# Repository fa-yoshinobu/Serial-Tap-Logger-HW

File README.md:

# Serial Tap Logger | RS-232C Rev.1

RS-232C機器2台の間にDE-9オス・メスで挿入し、送受信データと制御線の計8本をmicroSDに記録するロガー。各線を200 kΩ以上の抵抗で分岐し、DE-9の全9ピンを同じ番号で中継します。

## 現在の状況

Rev.1の基板と製造用データを作成済みです。ERC・DRC・未配線・回路図との不一致は各0件。裏面のBOMと実装座標は104点で照合済みです。記録ファームウェアは開発中で、記録性能とケースの嵌合は試作機で確認します。[作業状況と検証結果](docs/Work_Status.md)

## 接続例

[RS-232Cの接続例](docs/Wiring-RS232C.md)に、DE-9オス・メスの挿入位置、送受信を観測する配線、本体電源のつなぎ方を示します。

## 設計・製造資料

| 目的 | 資料 |
| --- | --- |
| 手はんだ部品を用意する | [手はんだ部品表](pcb/manufacturing/Hand_Assembly_BOM.csv) |
| JLCPCBに実装を依頼する | [JLCPCB実装部品表](pcb/manufacturing/PCBA_BOM.csv) |
| 回路を確認する | [回路図PDF](docs/Serial_Tap_Logger_RS232C_Rev1.pdf)・[KiCadデータ](pcb/) |
| 設計と寸法を確認する | [設計資料](docs/Design_Notes.md)・[ピン照合表](docs/Pin_Mapping.csv)・[基板STEP](enclosure/3d-models/Serial_Tap_Logger_RS232C_Rev1_PCBA.step)・[ケース組立](enclosure/drawings/Case_Print_Rev1.md) |
| 基板を製造・実装する | [入稿ファイルと発注条件](docs/Manufacturing.md)・[手はんだ実装図](enclosure/drawings/Hand-Solder-Assembly-Rev1.pdf) |
| 検証結果を確認する | [作業状況と残件](docs/Work_Status.md)・[検証レポート一覧](docs/verification/) |

## 基板の外観

| 表面（操作側）の実装3D図 | 裏面（工場実装側）の実装3D図 |
| --- | --- |
|  |  |

| 表面の配線（F.Cu） | 裏面の配線（B.Cu） |
| --- | --- |
|  |  |

## 主な仕様

| 項目 | 内容 |
| --- | --- |
| 対象 | RS-232C（±3〜±25 V）、115,200 bpsまでが設計目標 |
| 観測 | TXD・RXD・RTS・CTS・DTR・DSR・DCD・RIを正・負・開放（0 V付近）の3状態で判別。RIを除く7本の線路電圧も推定 |
| 記録と操作 | microSD（SDHC）、2.4インチ液晶、ロータリーエンコーダー |
| 基板 | 100 × 100 mm、2層。裏面を工場実装し、コネクタとモジュールを表面に手はんだ |
| 拡張端子 | Grove 2口（J7 I²C、J8 GP22／GP24、各3.3 V） |
| ケース | 3Dプリント用。幅121.1 × 奥行114.05 × 高さ32.8 mm（樹脂ケース単体） |

**測定中はUSBでPCに接続しない。** 電源はDC出力が接地されていない安定化12 V・1 AのACアダプター（外径5.5 mm、内径2.1 mm、センタープラス）を使用します。ログは測定後にmicroSDを取り出して読み込みます。[対応アダプターの例](https://akizukidenshi.com/catalog/g/g117429/)

## 主な部品と選定理由

- **WeAct RP2350B**。PIOで8本の状態を同時に取り込み、ADCで7本の線路電圧を推定するために使います。
- **窓型比較器**。各線の正・負・開放（0 V付近）を判別します。公称の判定点は線路換算で＋2.42 Vと−2.17 Vです。
- **PCF8563と電気二重層コンデンサー**。ログに日時を付け、電源を切っている間も時計を保持します。

## 3Dプリント用ケース

ふたはM3の熱圧入インサートとM3×6 mmねじ各4個で固定します。組立手順で、液晶の支持部品、左右のDE-9の取り付け、前面端子の差し込み寸法を確認できます。

[ケース3D（GitHubブラウザー表示）](enclosure/3d-models/Case_Browser.stl)・[ケースSTEP](enclosure/3d-models/Case_Print_Rev1.step)・[編集用SolidCraftモデル](enclosure/3d-models/Case_Print_Rev1.sc)・[底STL](enclosure/print/Case_Print_Rev1_Tray.stl)・[ふたSTL](enclosure/print/Case_Print_Rev1_Lid.stl)・[組立手順](enclosure/drawings/Case_Print_Rev1.md)・[基板を含む組立STEP](enclosure/3d-models/Case_Print_Rev1_Assembly.step)

## ライセンス

本プロジェクトのオリジナルのハードウェア設計を **CERN Open Hardware Licence Version 2 – Weakly Reciprocal（`CERN-OHL-W-2.0`）** で公開します。[ライセンス全文](LICENSE)

対象は、KiCadの回路図・基板・プロジェクトとプロジェクト独自のライブラリ、編集用ケースモデル、独自の部品モデル、およびこれらに対応する製造・組立データのうち本プロジェクトが権利を持つ部分です。編集用ソースと製造・組立に必要な情報は、このリポジトリの [KiCadデータ](pcb/)・[ケースデータ](enclosure/)・[製造資料](docs/Manufacturing.md) にあります。[Source Location](https://github.com/fa-yoshinobu/Serial-Tap-Logger-HW)

第三者のデータには各権利者の利用条件が適用されます。KiCad標準ライブラリにはKiCadのライセンスが適用されます。基板シルクのOpen Source Hardware歯車ロゴはMacklin Chaffeeのデザイン（CC-SA）です。[KiCadライブラリのライセンス](https://www.kicad.org/libraries/license/)・[OSHWAのロゴ使用条件](https://oshwa.org/resources/open-source-hardware-logo/)

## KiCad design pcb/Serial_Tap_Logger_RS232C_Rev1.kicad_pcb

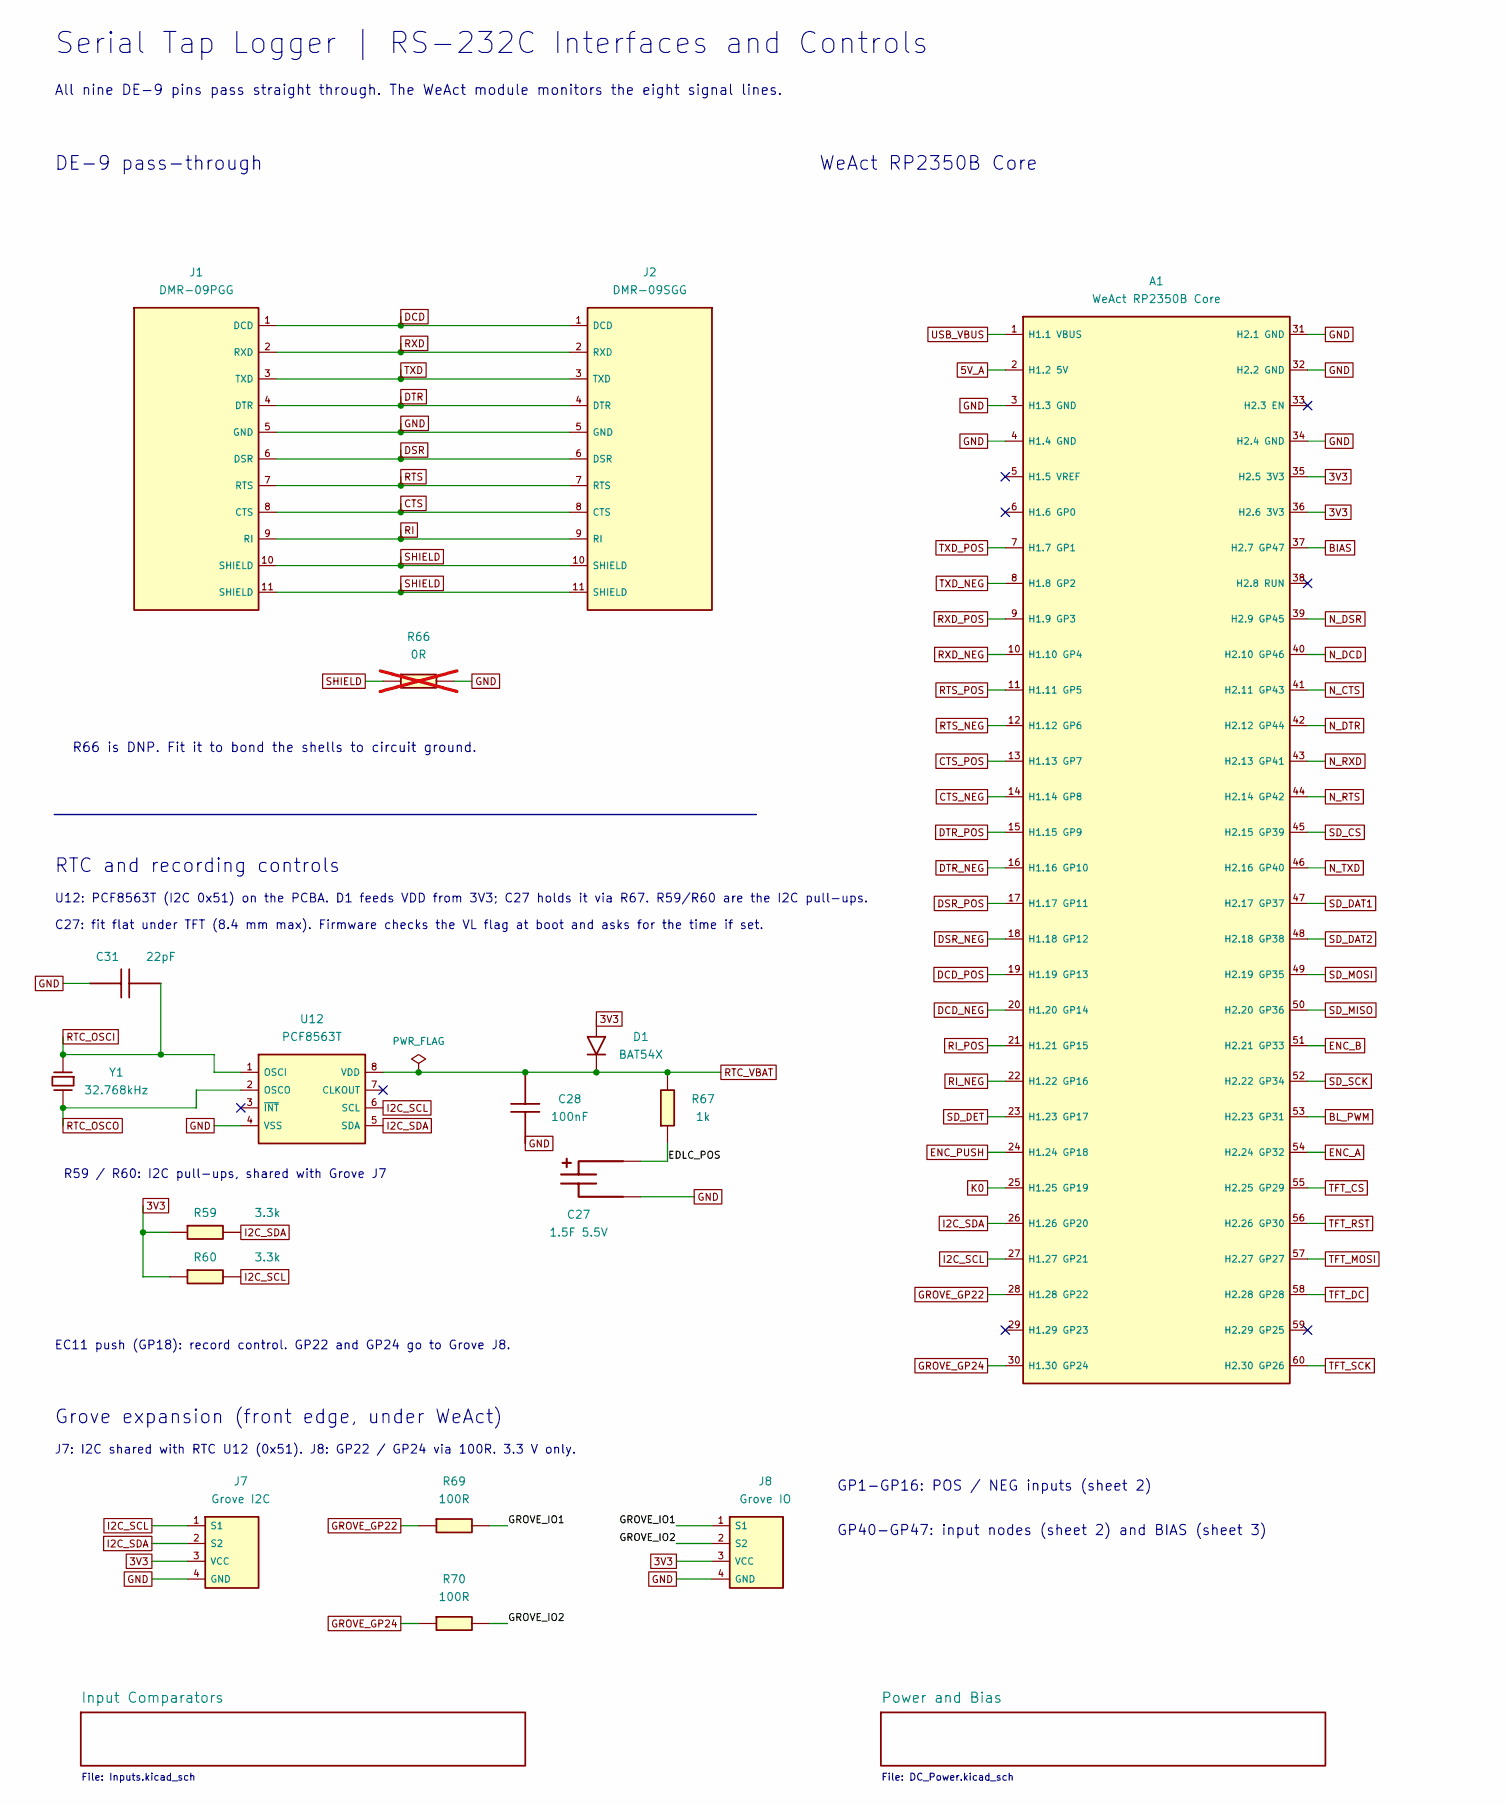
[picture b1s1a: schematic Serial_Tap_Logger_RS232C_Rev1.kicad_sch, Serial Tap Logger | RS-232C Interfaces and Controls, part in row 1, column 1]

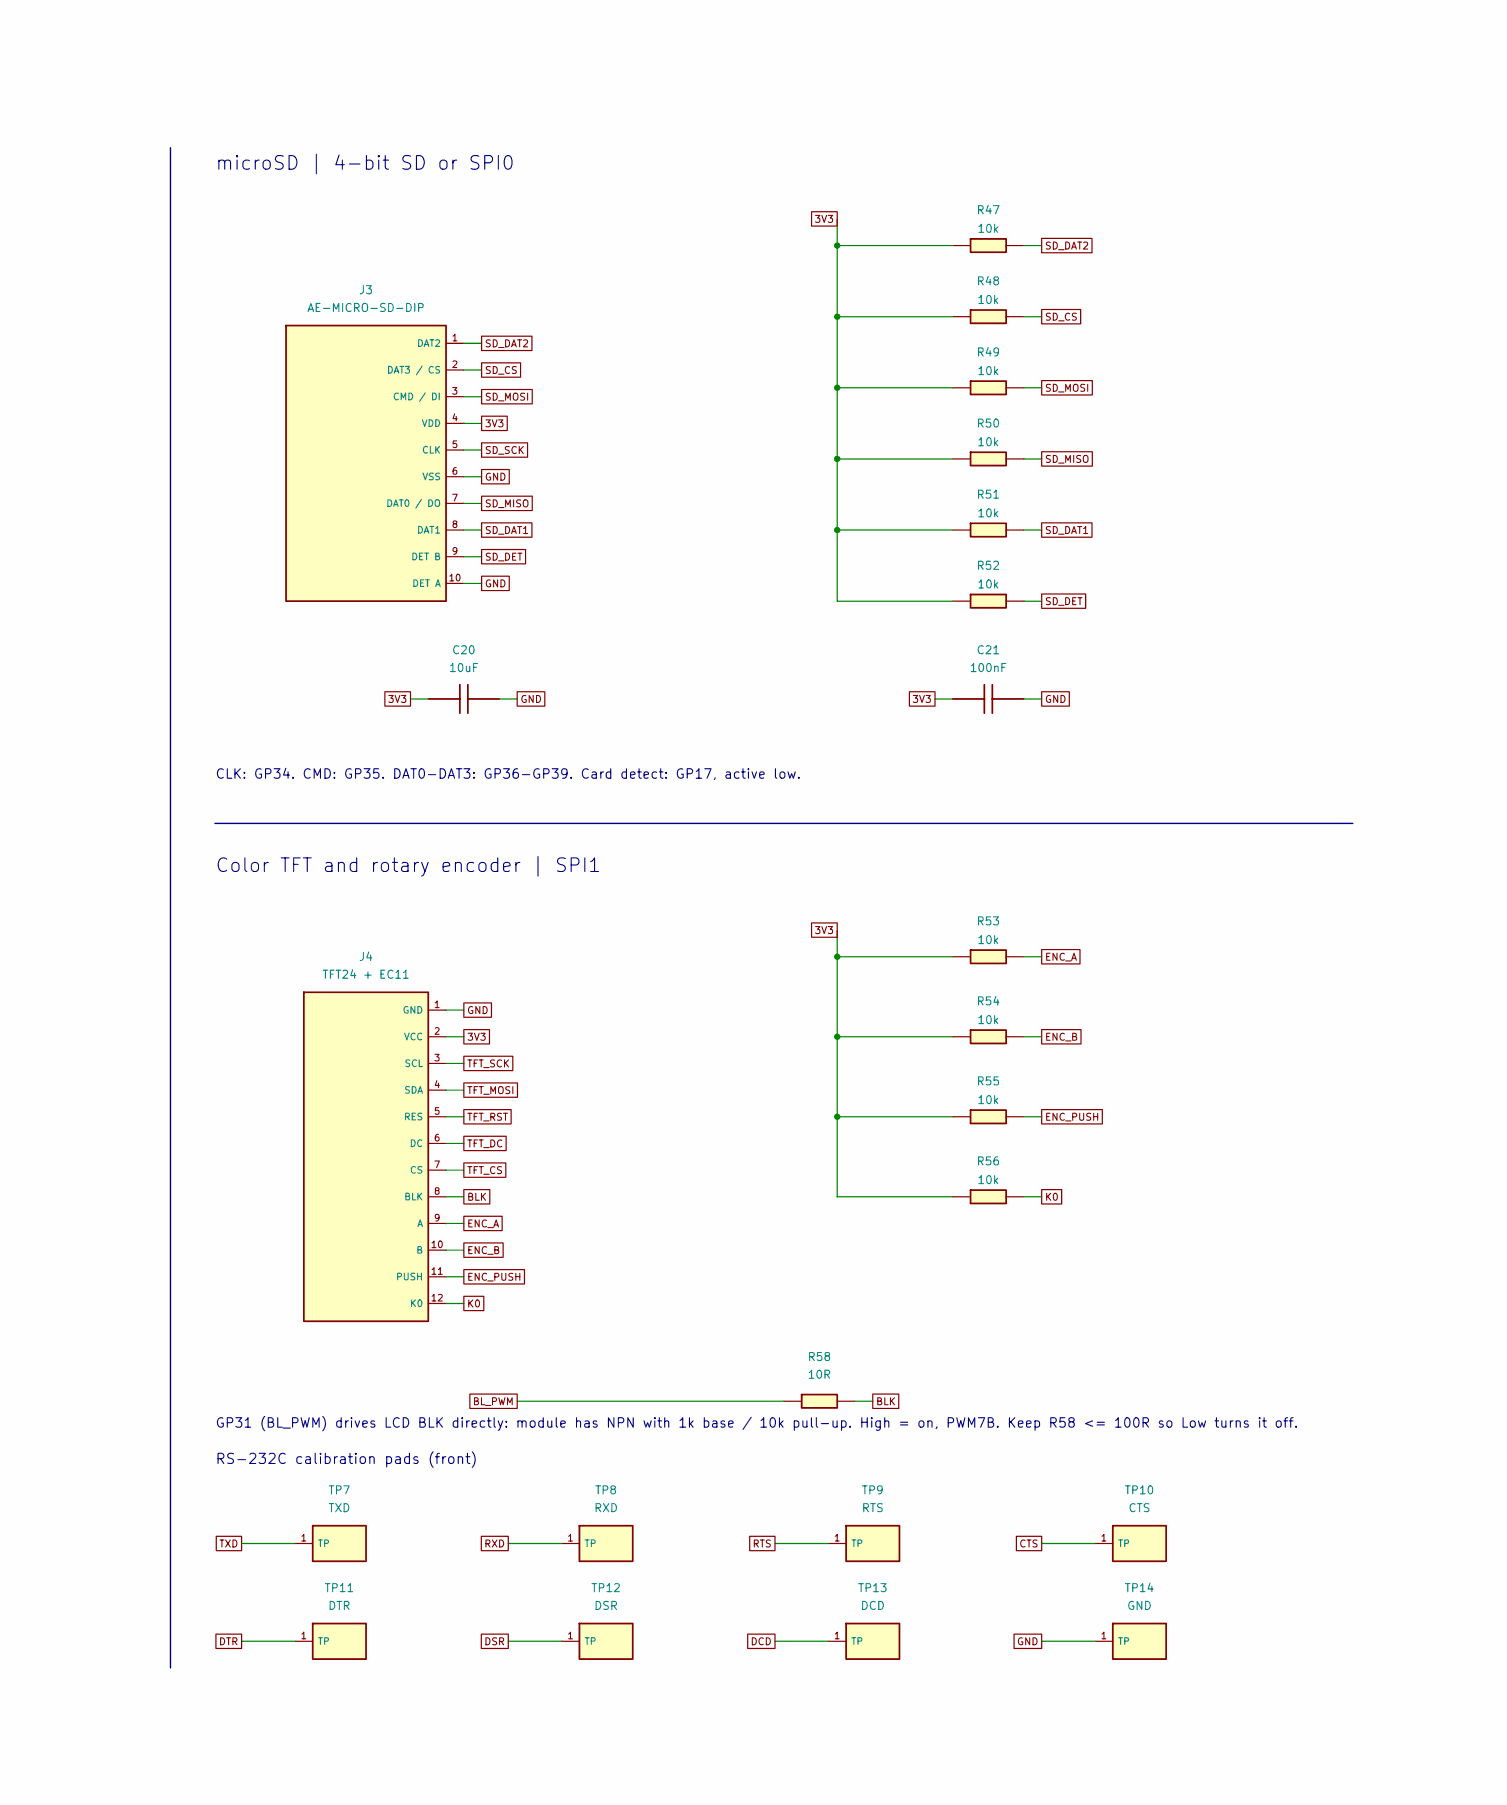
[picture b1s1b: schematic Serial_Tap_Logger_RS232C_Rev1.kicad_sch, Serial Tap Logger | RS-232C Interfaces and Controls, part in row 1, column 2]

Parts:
A1: WeAct RP2350B Core; WeAct_RP2350B
C20: 10uF; C_0805_2012Metric_DFM; MPN CL21A106KAYNNNE; LCSC C15850
C21, C28: 100nF; C_0603_1608Metric_DFM; MPN CC0603KRX7R9BB104; LCSC C14663
C27: 1.5F 5.5V; KAMCAP_SE-5R5-D155VY_Horizontal
C31: 22pF; C_0603_1608Metric_DFM; MPN CL10C220JB8NNNC; LCSC C1653
D1: BAT54X; D_SOD-523_DFM; MPN BAT54X; LCSC C19627026
J1: DMR-09PGG; DE9_M
J2: DMR-09SGG; DE9_F
J3: AE-MICRO-SD-DIP; AE_SD
J4: TFT24 + EC11; TFT24_EC11
J7: Grove I2C; Grove_110990037_RightAngle; MPN Seeed 110990037
J8: Grove IO; Grove_110990037_RightAngle; MPN Seeed 110990037
R47, R48, R49, R50, R51, R52, R53, R54, R55, R56: 10k; R_0603_1608Metric_DFM; MPN 0603WAF1002T5E; LCSC C25804
R58: 10R; R_0603_1608Metric_DFM; MPN 0603WAF100JT5E; LCSC C22859
R59, R60: 3.3k; R_0603_1608Metric_DFM; MPN 0603WAF3301T5E; LCSC C22978
R66: 0R; R_0603_1608Metric_DNP; MPN 0603WAJ0000T5E; LCSC C21189; not fitted
R67: 1k; R_0603_1608Metric_DFM; MPN 0603WAF1001T5E; LCSC C21190
R69, R70: 100R; R_0603_1608Metric_DFM; MPN 0603WAF1000T5E; LCSC C22775
TP7: TXD; TestPoint_Pad_D1.5mm_DFM
TP8: RXD; TestPoint_Pad_D1.5mm_DFM
TP9: RTS; TestPoint_Pad_D1.5mm_DFM
TP10: CTS; TestPoint_Pad_D1.5mm_DFM
TP11: DTR; TestPoint_Pad_D1.5mm_DFM
TP12: DSR; TestPoint_Pad_D1.5mm_DFM
TP13: DCD; TestPoint_Pad_D1.5mm_DFM
TP14: GND; TestPoint_Pad_D1.5mm_DFM
U12: PCF8563T; SOIC-8_3.9x4.9mm_P1.27mm_DFM; MPN PCF8563T/5,518; LCSC C7440
Y1: 32.768kHz; SII_VT-200-F_D2.0mm_Vertical; MPN VT-200-F 32.768kHz

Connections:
3V3: A1.35 (H2.5_3V3), A1.36 (H2.6_3V3), C20.1, C21.1, D1.2 (A), J3.4 (VDD), J4.2 (VCC), J7.3 (VCC), J8.3 (VCC), R47.1, R48.1, R49.1, R50.1, R51.1, R52.1, R53.1, R54.1, R55.1, R56.1, R59.1, R60.1; also elsewhere on the board
5V_A: A1.2 (H1.2_5V); also elsewhere on the board
/EDLC_POS: C27.1 (+), R67.1
/GROVE_IO1: J8.1 (S1), R69.2
/GROVE_IO2: J8.2 (S2), R70.2
BIAS: A1.37 (H2.7_GP47); also elsewhere on the board
BLK: J4.8 (BLK), R58.2
BL_PWM: A1.53 (H2.23_GP31), R58.1
CTS: J1.8 (CTS), J2.8 (CTS), TP10.1 (TP_1); also elsewhere on the board
CTS_NEG: A1.14 (H1.14_GP8); also elsewhere on the board
CTS_POS: A1.13 (H1.13_GP7); also elsewhere on the board
DCD: J1.1 (DCD), J2.1 (DCD), TP13.1 (TP_1); also elsewhere on the board
DCD_NEG: A1.20 (H1.20_GP14); also elsewhere on the board
DCD_POS: A1.19 (H1.19_GP13); also elsewhere on the board
DSR: J1.6 (DSR), J2.6 (DSR), TP12.1 (TP_1); also elsewhere on the board
DSR_NEG: A1.18 (H1.18_GP12); also elsewhere on the board
DSR_POS: A1.17 (H1.17_GP11); also elsewhere on the board
DTR: J1.4 (DTR), J2.4 (DTR), TP11.1 (TP_1); also elsewhere on the board
DTR_NEG: A1.16 (H1.16_GP10); also elsewhere on the board
DTR_POS: A1.15 (H1.15_GP9); also elsewhere on the board
ENC_A: A1.54 (H2.24_GP32), J4.9 (A), R53.2
ENC_B: A1.51 (H2.21_GP33), J4.10 (B), R54.2
ENC_PUSH: A1.24 (H1.24_GP18), J4.11 (PUSH), R55.2
GND: A1.3 (H1.3_GND), A1.4 (H1.4_GND), A1.31 (H2.1_GND), A1.32 (H2.2_GND), A1.34 (H2.4_GND), C20.2, C21.2, C27.2 (-), C28.2, C31.1, J1.5 (GND), J2.5 (GND), J3.6 (VSS), J3.10 (DET_A), J4.1 (GND), J7.4 (GND), J8.4 (GND), R66.2, TP14.1 (TP_1), U12.4 (VSS); also elsewhere on the board
GROVE_GP22: A1.28 (H1.28_GP22), R69.1
GROVE_GP24: A1.30 (H1.30_GP24), R70.1
I2C_SCL: A1.27 (H1.27_GP21), J7.1 (S1), R60.2, U12.6 (SCL)
I2C_SDA: A1.26 (H1.26_GP20), J7.2 (S2), R59.2, U12.5 (SDA)
K0: A1.25 (H1.25_GP19), J4.12 (K0), R56.2
N_CTS: A1.41 (H2.11_GP43); also elsewhere on the board
N_DCD: A1.40 (H2.10_GP46); also elsewhere on the board
N_DSR: A1.39 (H2.9_GP45); also elsewhere on the board
N_DTR: A1.42 (H2.12_GP44); also elsewhere on the board
N_RTS: A1.44 (H2.14_GP42); also elsewhere on the board
N_RXD: A1.43 (H2.13_GP41); also elsewhere on the board
N_TXD: A1.46 (H2.16_GP40); also elsewhere on the board
RI: J1.9 (RI), J2.9 (RI); also elsewhere on the board
RI_NEG: A1.22 (H1.22_GP16); also elsewhere on the board
RI_POS: A1.21 (H1.21_GP15); also elsewhere on the board
RTC_OSCI: C31.2, U12.1 (OSCI), Y1.1
RTC_OSCO: U12.2 (OSCO), Y1.2
RTC_VBAT: C28.1, D1.1 (K), R67.2, U12.8 (VDD)
RTS: J1.7 (RTS), J2.7 (RTS), TP9.1 (TP_1); also elsewhere on the board
RTS_NEG: A1.12 (H1.12_GP6); also elsewhere on the board
RTS_POS: A1.11 (H1.11_GP5); also elsewhere on the board
RXD: J1.2 (RXD), J2.2 (RXD), TP8.1 (TP_1); also elsewhere on the board
RXD_NEG: A1.10 (H1.10_GP4); also elsewhere on the board
RXD_POS: A1.9 (H1.9_GP3); also elsewhere on the board
SD_CS: A1.45 (H2.15_GP39), J3.2 (DAT3_/_CS), R48.2
SD_DAT1: A1.47 (H2.17_GP37), J3.8 (DAT1), R51.2
SD_DAT2: A1.48 (H2.18_GP38), J3.1 (DAT2), R47.2
SD_DET: A1.23 (H1.23_GP17), J3.9 (DET_B), R52.2
SD_MISO: A1.50 (H2.20_GP36), J3.7 (DAT0_/_DO), R50.2
SD_MOSI: A1.49 (H2.19_GP35), J3.3 (CMD_/_DI), R49.2
SD_SCK: A1.52 (H2.22_GP34), J3.5 (CLK)
SHIELD: J1.10 (SHIELD), J1.11 (SHIELD), J2.10 (SHIELD), J2.11 (SHIELD), R66.1
TFT_CS: A1.55 (H2.25_GP29), J4.7 (CS)
TFT_DC: A1.58 (H2.28_GP28), J4.6 (DC)
TFT_MOSI: A1.57 (H2.27_GP27), J4.4 (SDA)
TFT_RST: A1.56 (H2.26_GP30), J4.5 (RES)
TFT_SCK: A1.60 (H2.30_GP26), J4.3 (SCL)
TXD: J1.3 (TXD), J2.3 (TXD), TP7.1 (TP_1); also elsewhere on the board
TXD_NEG: A1.8 (H1.8_GP2); also elsewhere on the board
TXD_POS: A1.7 (H1.7_GP1); also elsewhere on the board
USB_VBUS: A1.1 (H1.1_VBUS); also elsewhere on the board

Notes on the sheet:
Serial Tap Logger | RS-232C Interfaces and Controls
All nine DE-9 pins pass straight through. The WeAct module monitors the eight signal lines.
DE-9 pass-through
R66 is DNP. Fit it to bond the shells to circuit ground.
WeAct RP2350B Core
GP1-GP16: POS / NEG inputs (sheet 2)
GP40-GP47: input nodes (sheet 2) and BIAS (sheet 3)
microSD | 4-bit SD or SPI0
CLK: GP34. CMD: GP35. DAT0-DAT3: GP36-GP39. Card detect: GP17, active low.
Color TFT and rotary encoder | SPI1
GP31 (BL_PWM) drives LCD BLK directly: module has NPN with 1k base / 10k pull-up. High = on, PWM7B. Keep R58 <= 100R so Low turns it off.
RTC and recording controls
U12: PCF8563T (I2C 0x51) on the PCBA. D1 feeds VDD from 3V3; C27 holds it via R67. R59/R60 are the I2C pull-ups.
C27: fit flat under TFT (8.4 mm max). Firmware checks the VL flag at boot and asks for the time if set.
EC11 push (GP18): record control. GP22 and GP24 go to Grove J8.
File: Inputs.kicad_sch
File: DC_Power.kicad_sch
Grove expansion (front edge, under WeAct)
J7: I2C shared with RTC U12 (0x51). J8: GP22 / GP24 via 100R. 3.3 V only.
R59 / R60: I2C pull-ups, shared with Grove J7
RS-232C calibration pads (front)

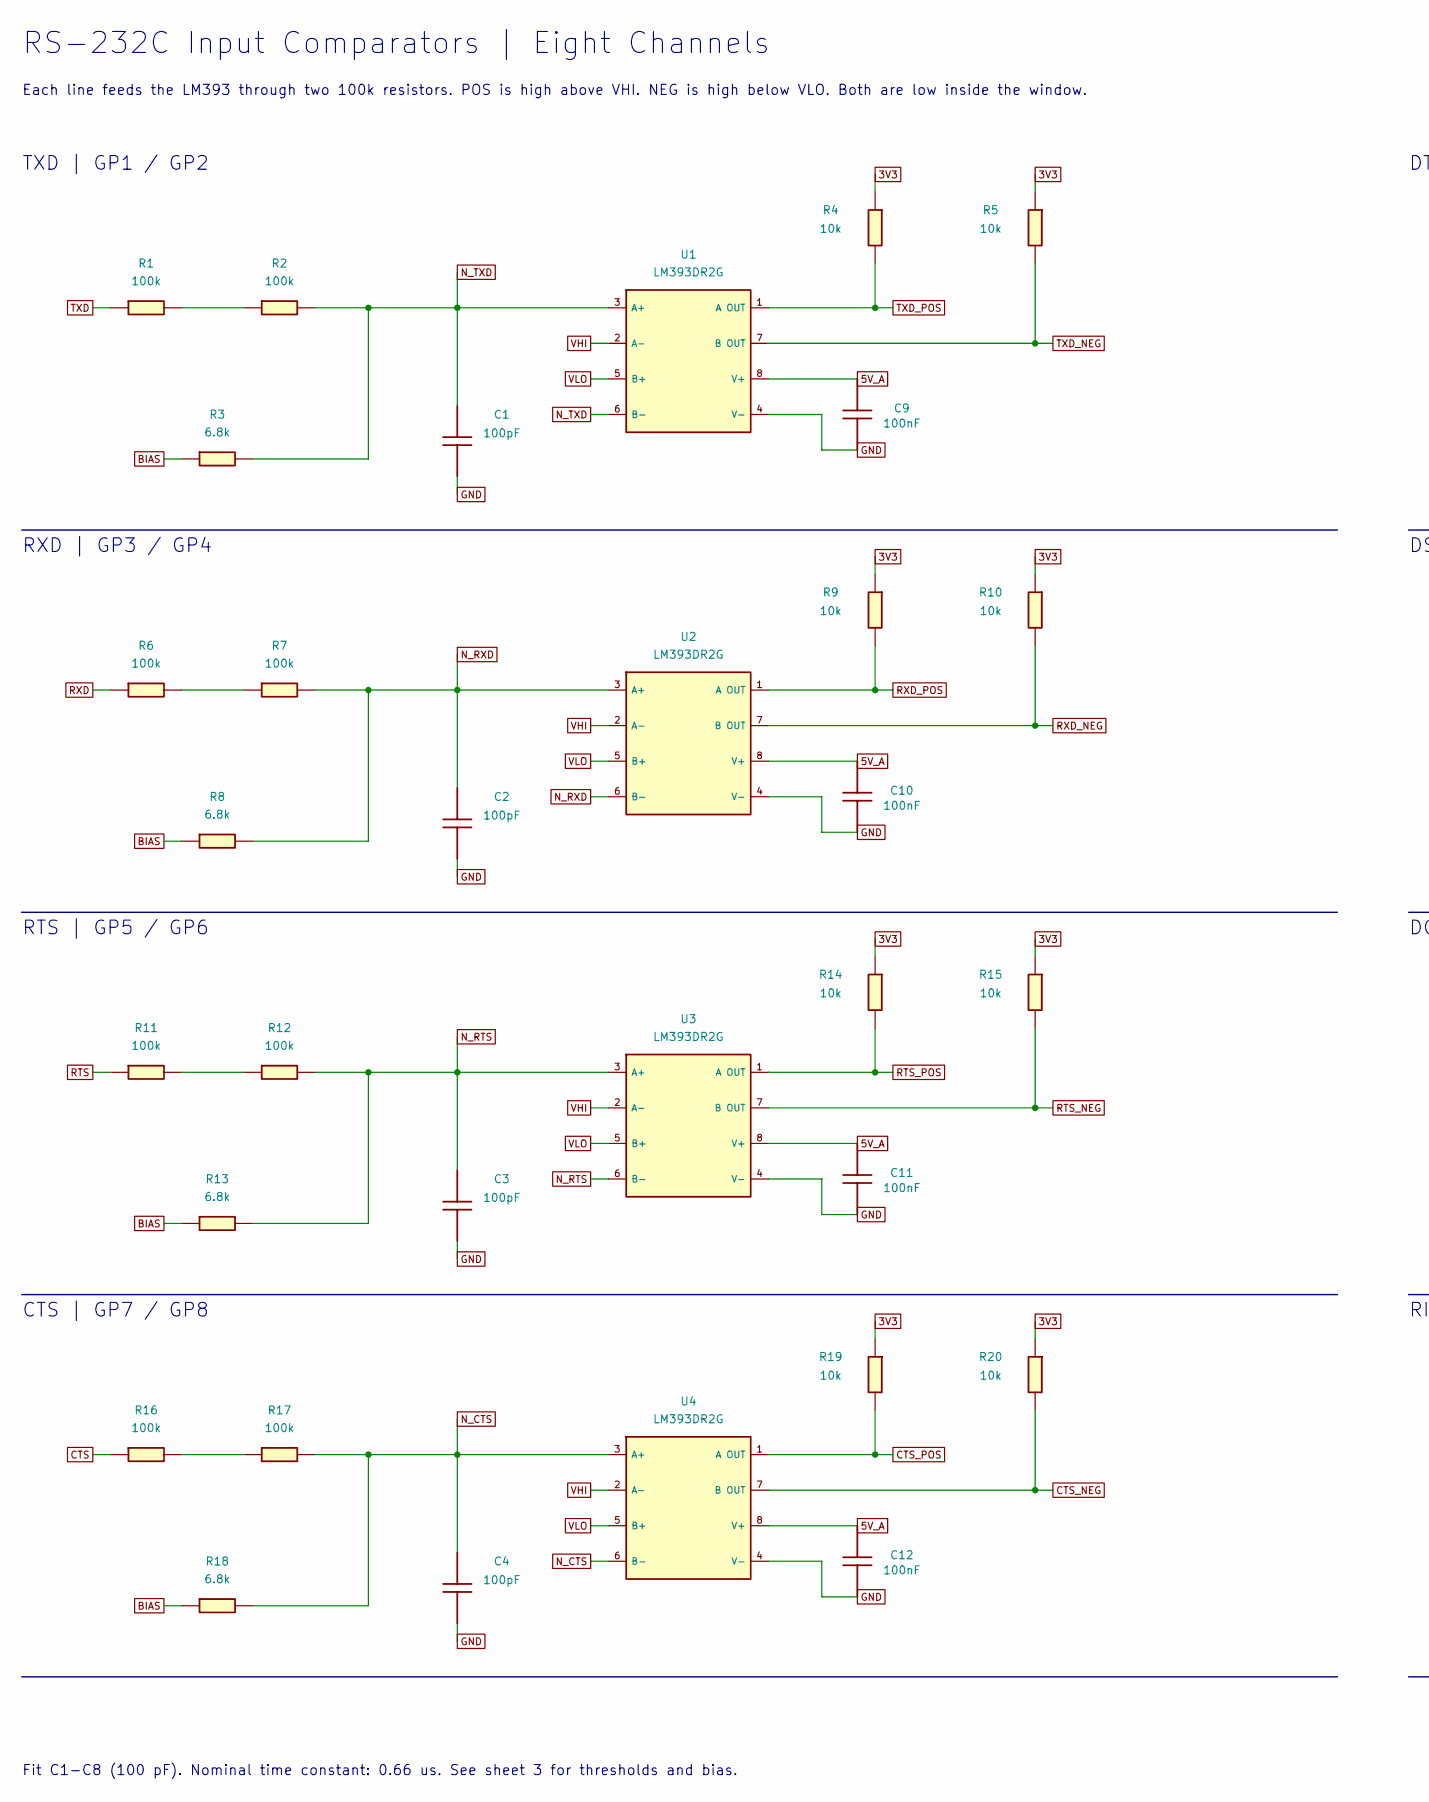
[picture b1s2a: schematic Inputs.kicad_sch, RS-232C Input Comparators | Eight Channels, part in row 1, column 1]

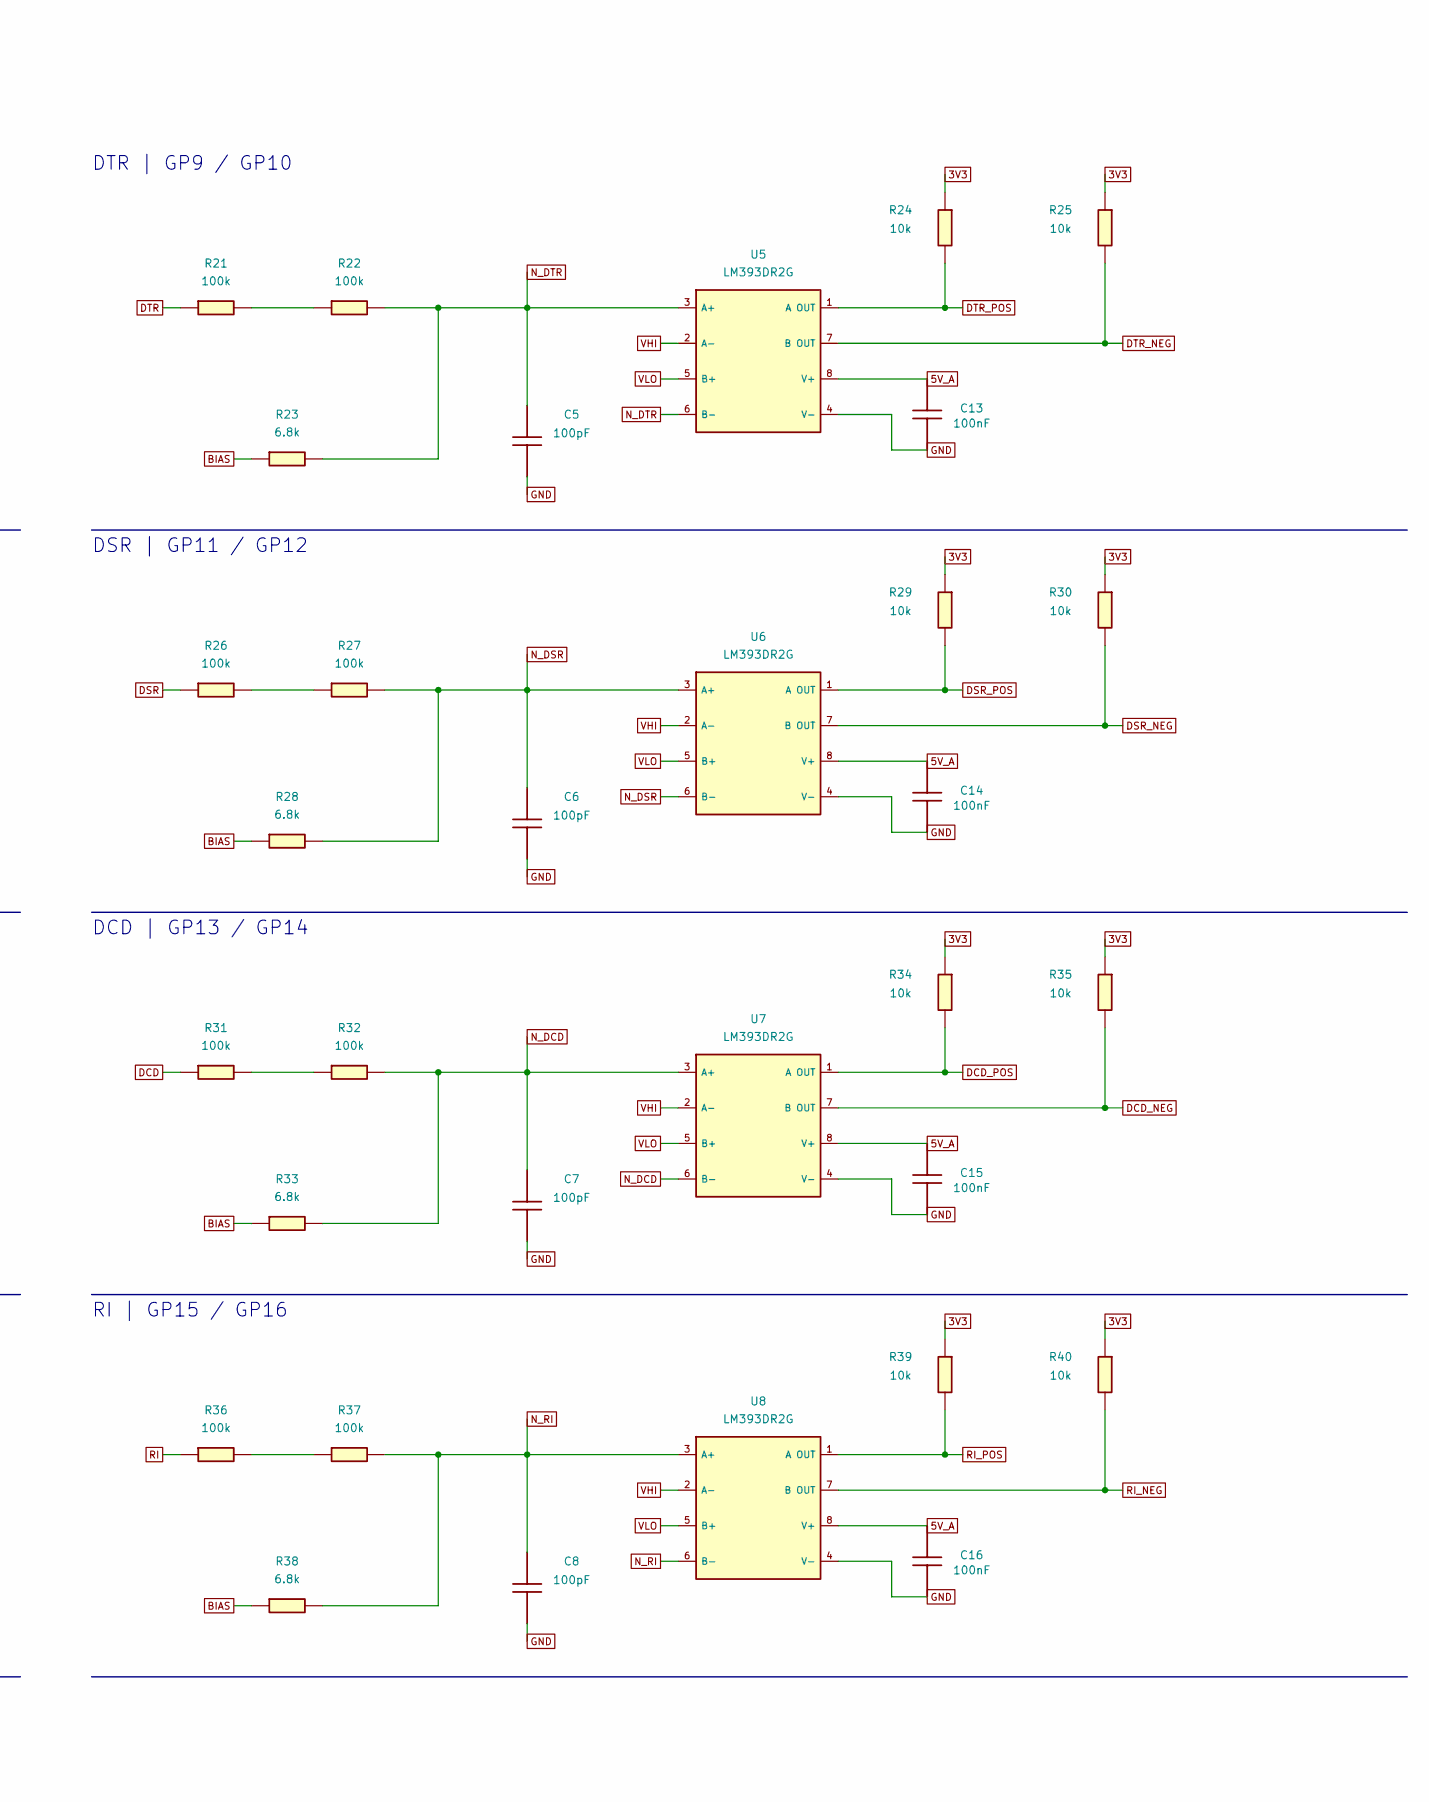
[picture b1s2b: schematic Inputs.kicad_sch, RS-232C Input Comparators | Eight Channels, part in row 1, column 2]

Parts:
C1, C2, C3, C4, C5, C6, C7, C8: 100pF; C_0603_1608Metric_DFM; MPN CL10C101JB8NNNC; LCSC C14858
C9, C10, C11, C12, C13, C14, C15, C16: 100nF; C_0603_1608Metric_DFM; MPN CC0603KRX7R9BB104; LCSC C14663
R1, R2, R6, R7, R11, R12, R16, R17, R21, R22, R26, R27, R31, R32, R36, R37: 100k; R_0603_1608Metric_DFM; MPN 0603WAF1003T5E; LCSC C25803
R3, R8, R13, R18, R23, R28, R33, R38: 6.8k; R_0603_1608Metric_DFM; MPN 0603WAF6801T5E; LCSC C23212
R4, R5, R9, R10, R14, R15, R19, R20, R24, R25, R29, R30, R34, R35, R39, R40: 10k; R_0603_1608Metric_DFM; MPN 0603WAF1002T5E; LCSC C25804
U1, U2, U3, U4, U5, U6, U7, U8: LM393DR2G; SOIC-8_3.9x4.9mm_P1.27mm_DFM; MPN LM393DR2G; LCSC C7955

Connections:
3V3: R4.1, R5.1, R9.1, R10.1, R14.1, R15.1, R19.1, R20.1, R24.1, R25.1, R29.1, R30.1, R34.1, R35.1, R39.1, R40.1; also elsewhere on the board
5V_A: C9.1, C10.1, C11.1, C12.1, C13.1, C14.1, C15.1, C16.1, U1.8 (V+), U2.8 (V+), U3.8 (V+), U4.8 (V+), U5.8 (V+), U6.8 (V+), U7.8 (V+), U8.8 (V+); also elsewhere on the board
BIAS: R3.1, R8.1, R13.1, R18.1, R23.1, R28.1, R33.1, R38.1; also elsewhere on the board
CTS: R16.1; also elsewhere on the board
CTS_NEG: R20.2, U4.7 (B_OUT); also elsewhere on the board
CTS_POS: R19.2, U4.1 (A_OUT); also elsewhere on the board
DCD: R31.1; also elsewhere on the board
DCD_NEG: R35.2, U7.7 (B_OUT); also elsewhere on the board
DCD_POS: R34.2, U7.1 (A_OUT); also elsewhere on the board
DSR: R26.1; also elsewhere on the board
DSR_NEG: R30.2, U6.7 (B_OUT); also elsewhere on the board
DSR_POS: R29.2, U6.1 (A_OUT); also elsewhere on the board
DTR: R21.1; also elsewhere on the board
DTR_NEG: R25.2, U5.7 (B_OUT); also elsewhere on the board
DTR_POS: R24.2, U5.1 (A_OUT); also elsewhere on the board
GND: C1.2, C2.2, C3.2, C4.2, C5.2, C6.2, C7.2, C8.2, C9.2, C10.2, C11.2, C12.2, C13.2, C14.2, C15.2, C16.2, U1.4 (V-), U2.4 (V-), U3.4 (V-), U4.4 (V-), U5.4 (V-), U6.4 (V-), U7.4 (V-), U8.4 (V-); also elsewhere on the board
N_CTS: C4.1, R17.2, R18.2, U4.3 (A+), U4.6 (B-); also elsewhere on the board
N_DCD: C7.1, R32.2, R33.2, U7.3 (A+), U7.6 (B-); also elsewhere on the board
N_DSR: C6.1, R27.2, R28.2, U6.3 (A+), U6.6 (B-); also elsewhere on the board
N_DTR: C5.1, R22.2, R23.2, U5.3 (A+), U5.6 (B-); also elsewhere on the board
N_RI: C8.1, R37.2, R38.2, U8.3 (A+), U8.6 (B-)
N_RTS: C3.1, R12.2, R13.2, U3.3 (A+), U3.6 (B-); also elsewhere on the board
N_RXD: C2.1, R7.2, R8.2, U2.3 (A+), U2.6 (B-); also elsewhere on the board
N_TXD: C1.1, R2.2, R3.2, U1.3 (A+), U1.6 (B-); also elsewhere on the board
unnamed: R1.2, R2.1
unnamed: R6.2, R7.1
unnamed: R11.2, R12.1
unnamed: R16.2, R17.1
unnamed: R21.2, R22.1
unnamed: R26.2, R27.1
unnamed: R31.2, R32.1
unnamed: R36.2, R37.1
RI: R36.1; also elsewhere on the board
RI_NEG: R40.2, U8.7 (B_OUT); also elsewhere on the board
RI_POS: R39.2, U8.1 (A_OUT); also elsewhere on the board
RTS: R11.1; also elsewhere on the board
RTS_NEG: R15.2, U3.7 (B_OUT); also elsewhere on the board
RTS_POS: R14.2, U3.1 (A_OUT); also elsewhere on the board
RXD: R6.1; also elsewhere on the board
RXD_NEG: R10.2, U2.7 (B_OUT); also elsewhere on the board
RXD_POS: R9.2, U2.1 (A_OUT); also elsewhere on the board
TXD: R1.1; also elsewhere on the board
TXD_NEG: R5.2, U1.7 (B_OUT); also elsewhere on the board
TXD_POS: R4.2, U1.1 (A_OUT); also elsewhere on the board
VHI: U1.2 (A-), U2.2 (A-), U3.2 (A-), U4.2 (A-), U5.2 (A-), U6.2 (A-), U7.2 (A-), U8.2 (A-); also elsewhere on the board
VLO: U1.5 (B+), U2.5 (B+), U3.5 (B+), U4.5 (B+), U5.5 (B+), U6.5 (B+), U7.5 (B+), U8.5 (B+); also elsewhere on the board

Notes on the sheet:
RS-232C Input Comparators | Eight Channels
Each line feeds the LM393 through two 100k resistors. POS is high above VHI. NEG is high below VLO. Both are low inside the window.
TXD | GP1 / GP2
RXD | GP3 / GP4
RTS | GP5 / GP6
CTS | GP7 / GP8
DTR | GP9 / GP10
DSR | GP11 / GP12
DCD | GP13 / GP14
RI | GP15 / GP16
Fit C1-C8 (100 pF). Nominal time constant: 0.66 us. See sheet 3 for thresholds and bias.
